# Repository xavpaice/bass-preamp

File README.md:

# Bass pre-amp circuit

This is a simple preamp with some basic tone control intended to be paired with
a piezo pickup in a clone of one of the range of 21" scale rubber string'ed bass
guitars (aka ukulele bass).  It's very much a work in progress, and any edits
are appreciated.

The drawings are all made with Kicad.

# License

<br />This work
is licensed under a <a rel="license"
href="http://creativecommons.org/licenses/by/3.0/nz/">Creative Commons
Attribution 3.0 New Zealand License</a>.

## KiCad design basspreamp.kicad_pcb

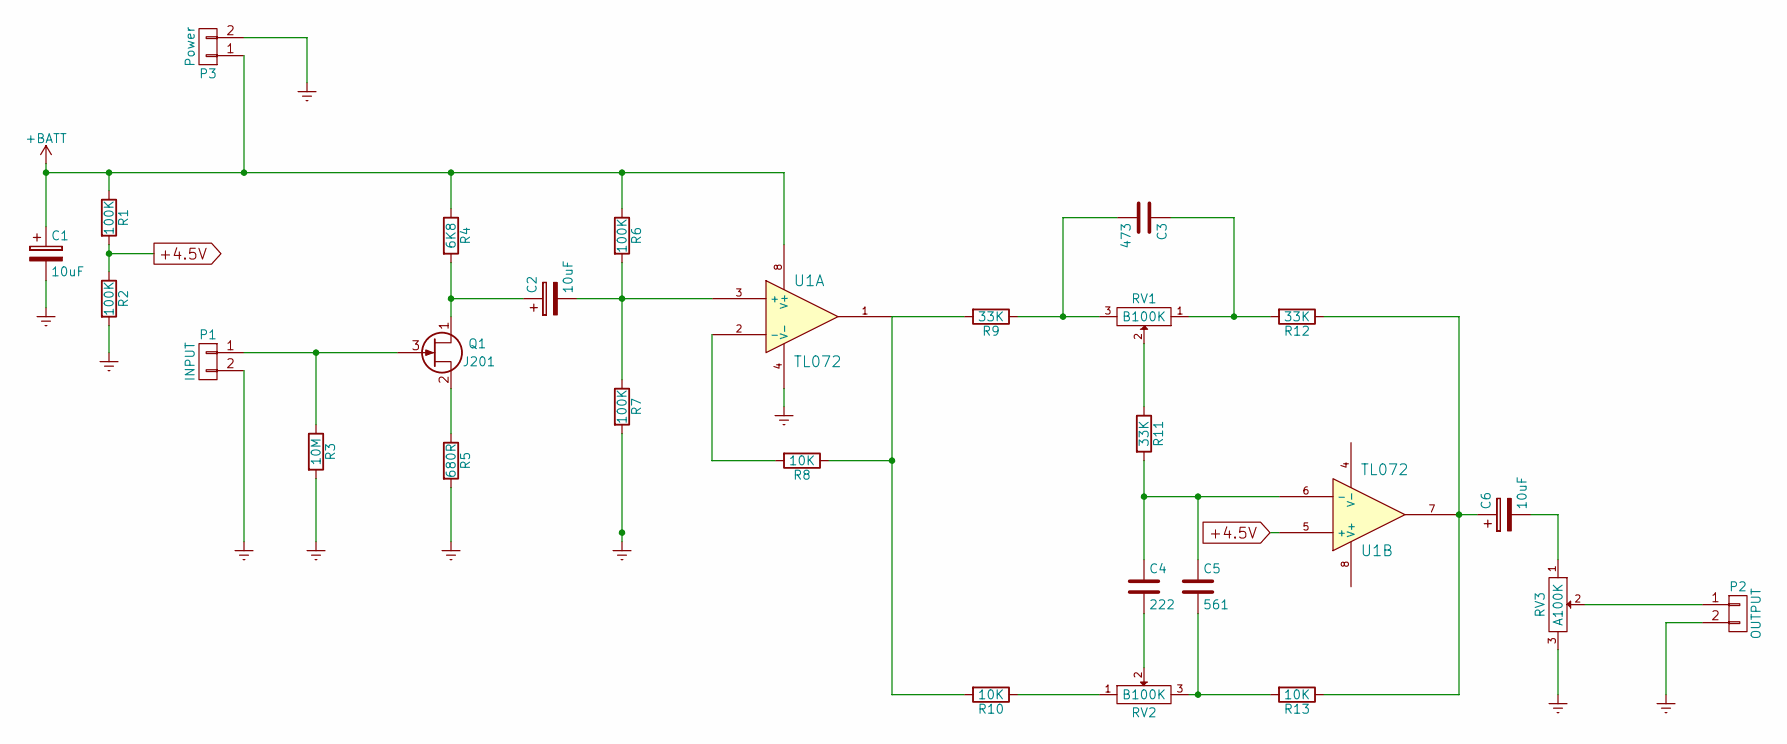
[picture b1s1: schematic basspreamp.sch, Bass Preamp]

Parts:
C1, C2, C6: 10uF; Elko_vert_11x5mm_RM2.5
C3: 473; C_Disc_D12_P7.75
C4: 222; C_Rect_L7_W3.5_P5
C5: 561; C_Rect_L7_W3.5_P5
P1: INPUT; Pin_Header_Straight_1x02
P2: OUTPUT; Pin_Header_Straight_1x02
P3: Power; Pin_Header_Straight_1x02
Q1: J201; TO-92_Inline_Narrow_Oval
R1, R2, R6, R7: 100K; Resistor_Horizontal_RM10mm
R3: 10M; Resistor_Horizontal_RM10mm
R4: 6K8; Resistor_Horizontal_RM10mm
R5: 680R; Resistor_Horizontal_RM10mm
R8, R10, R13: 10K; Resistor_Horizontal_RM10mm
R9, R11, R12: 33K; Resistor_Horizontal_RM10mm
RV1, RV2: B100K; Potentiometer_WirePads_largePads
RV3: A100K; Potentiometer_WirePads_largePads
U1: TL072; DIP-8__300_ELL

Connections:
+4.5V: R1.2, R2.1, U1.5 (+)
+BATT: C1.1, P3.1, R1.1, R4.1, R6.1, U1.8 (V+)
Earth: C1.2, P1.2, P2.2, P3.2, R2.2, R3.2, R5.2, R7.2, RV3.3, U1.4 (V-)
unnamed: C2.1, Q1.1 (D), R4.2
unnamed: C2.2, R6.2, R7.1, U1.3 (+)
unnamed: C3.1, R12.2, RV1.1
unnamed: C3.2, R9.1, RV1.3
unnamed: C4.1, C5.1, R11.2, U1.6 (-)
unnamed: C4.2, RV2.2
unnamed: C5.2, R13.2, RV2.3
unnamed: C6.1, R12.1, R13.1, U1.7
unnamed: C6.2, RV3.1
unnamed: P1.1, Q1.3 (G), R3.1
unnamed: P2.1, RV3.2
unnamed: Q1.2 (S), R5.1
unnamed: R8.2, U1.2 (-)
unnamed: R10.1, RV2.1
unnamed: R8.1, R9.2, R10.2, U1.1
unnamed: R11.1, RV1.2

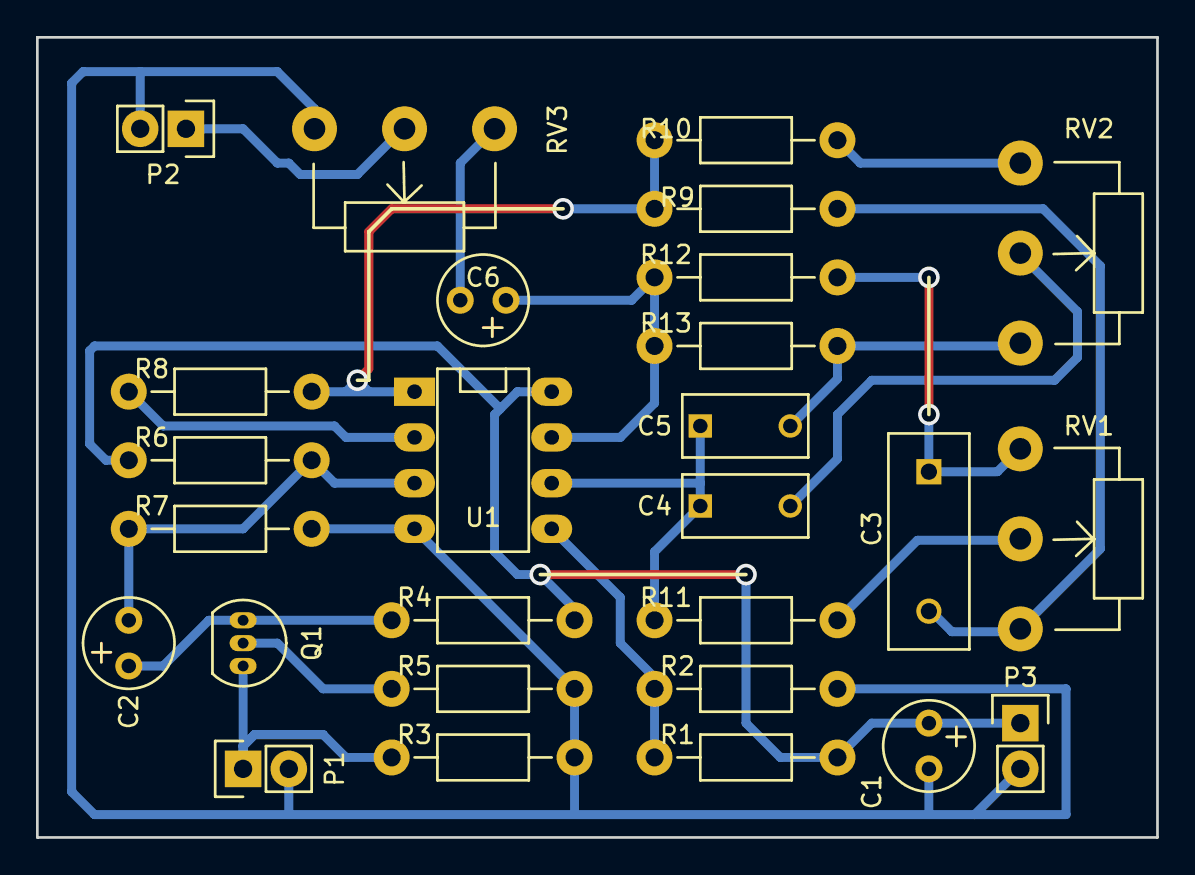
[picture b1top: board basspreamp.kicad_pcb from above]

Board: 2 copper layers, 62.2 x 44.5 mm, 27 parts (0 on the bottom side), 19 nets.

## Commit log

2015-11-30 Add filled zone to pcb, make prints

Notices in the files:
basspreamp.sch:
To view a copy of this license, visit http://creativecommons.org/licenses/by/4.0/.
This work is licensed under the Creative Commons Attribution 4.0 International License.
